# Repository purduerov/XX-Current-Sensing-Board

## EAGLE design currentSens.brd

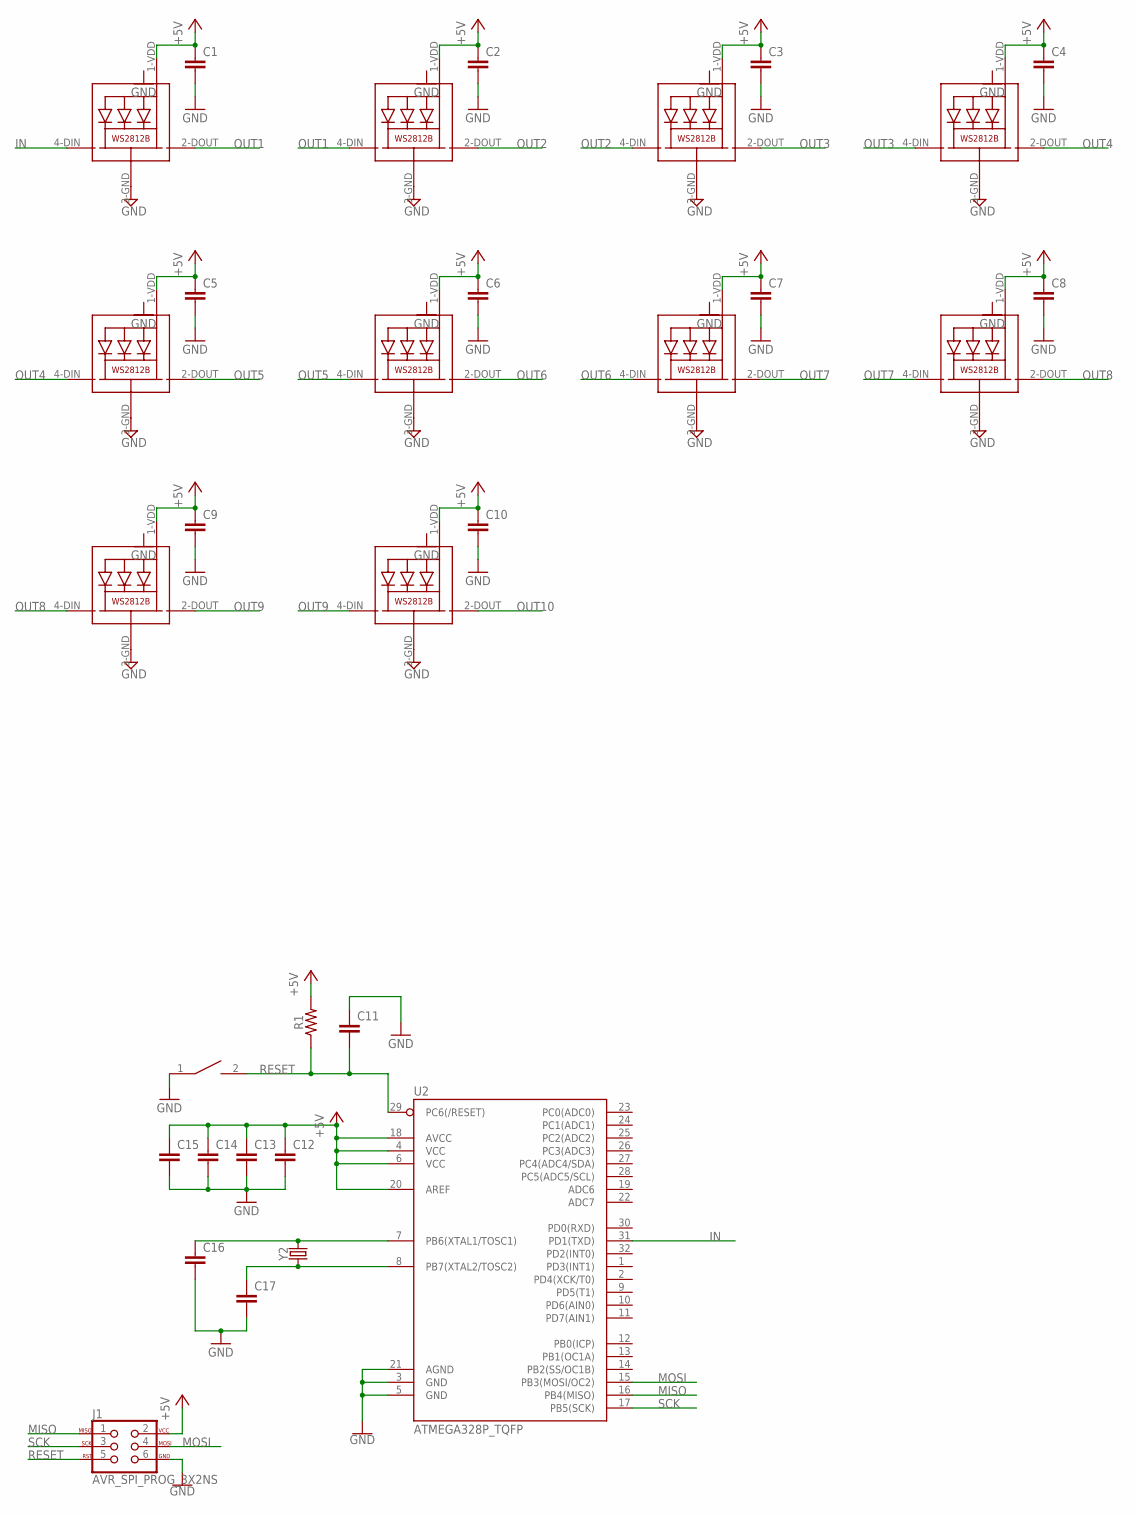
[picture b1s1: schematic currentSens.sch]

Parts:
BOOT: SWITCH; SW_2512
C1, C2, C3, C4, C5, C6, C7, C8, C9, C10, C11, C12, C13, C14, C15, C16, C17: C-EUC0603; C0603
J1: AVR_SPI_PROG_3X2NS; 2X3-NS
LED1, LED2, LED3, LED4, LED5, LED6, LED7, LED8, LED9, LED10: WS2812B5050; WS2812B
R1: 0603
U2: ATMEGA328P_TQFP; TQFP32-08
Y2: CRYSTALPTH-HC49US; HC49US

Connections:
+5V: C1.1, C2.1, C3.1, C4.1, C5.1, C6.1, C7.1, C8.1, C9.1, C10.1, C12.1, C13.1, C14.1, C15.1, J1.2, LED1.1-VDD (VDD), LED2.1-VDD (VDD), LED3.1-VDD (VDD), LED4.1-VDD (VDD), LED5.1-VDD (VDD), LED6.1-VDD (VDD), LED7.1-VDD (VDD), LED8.1-VDD (VDD), LED9.1-VDD (VDD), LED10.1-VDD (VDD), R1.2, U2.4 (VCC), U2.6 (VCC), U2.18 (AVCC), U2.20 (AREF)
GND: BOOT.1, C1.2, C2.2, C3.2, C4.2, C5.2, C6.2, C7.2, C8.2, C9.2, C10.2, C11.1, C12.2, C13.2, C14.2, C15.2, C16.2, C17.2, J1.6, LED1.3-GND (GND), LED2.3-GND (GND), LED3.3-GND (GND), LED4.3-GND (GND), LED5.3-GND (GND), LED6.3-GND (GND), LED7.3-GND (GND), LED8.3-GND (GND), LED9.3-GND (GND), LED10.3-GND (GND), U2.3 (GND), U2.5 (GND), U2.21 (AGND)
IN: LED1.4-DIN (DI), U2.31 (PD1(TXD))
MISO: J1.1, U2.16 (PB4(MISO))
MOSI: J1.4, U2.15 (PB3(MOSI/OC2))
unnamed: C16.1, U2.7 (PB6(XTAL1/TOSC1)), Y2.2
unnamed: C17.1, U2.8 (PB7(XTAL2/TOSC2)), Y2.1
OUT1: LED1.2-DOUT (DO), LED2.4-DIN (DI)
OUT2: LED2.2-DOUT (DO), LED3.4-DIN (DI)
OUT3: LED3.2-DOUT (DO), LED4.4-DIN (DI)
OUT4: LED4.2-DOUT (DO), LED5.4-DIN (DI)
OUT5: LED5.2-DOUT (DO), LED6.4-DIN (DI)
OUT6: LED6.2-DOUT (DO), LED7.4-DIN (DI)
OUT7: LED7.2-DOUT (DO), LED8.4-DIN (DI)
OUT8: LED8.2-DOUT (DO), LED9.4-DIN (DI)
OUT9: LED9.2-DOUT (DO), LED10.4-DIN (DI)
OUT10: LED10.2-DOUT (DO)
RESET: BOOT.2, C11.2, J1.5, R1.1, U2.29 (PC6(/RESET))
SCK: J1.3, U2.17 (PB5(SCK))

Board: 2 copper layers, 32 parts (0 on the bottom side), 18 nets, no tracks yet.

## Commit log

2017-09-30 Intial Schematic with atmel chip and neo pixel
2017-10-01 Added more neopixels
2017-10-07 Adding test script to determine resolution of temperature sensing
2017-10-15 Added gitignore
2017-10-26 had to change the grid
2017-10-27 included the MCP3008 current sensors and traces
2017-10-28 Finshed up microcontroller circuit

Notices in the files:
parts and their libraries:
microbuilder: This work is placed in the public domain, and may be freely used for commercial and non-commercial work with the following conditions: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
SparkFun-IC-Microcontroller: Licensing: Creative Commons ShareAlike 4.0 International - https://creativecommons.org/licenses/by-sa/4.0
